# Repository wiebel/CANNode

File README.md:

Homegrown CAN/OW based home automation.

https://wiebel.org/CANNode/

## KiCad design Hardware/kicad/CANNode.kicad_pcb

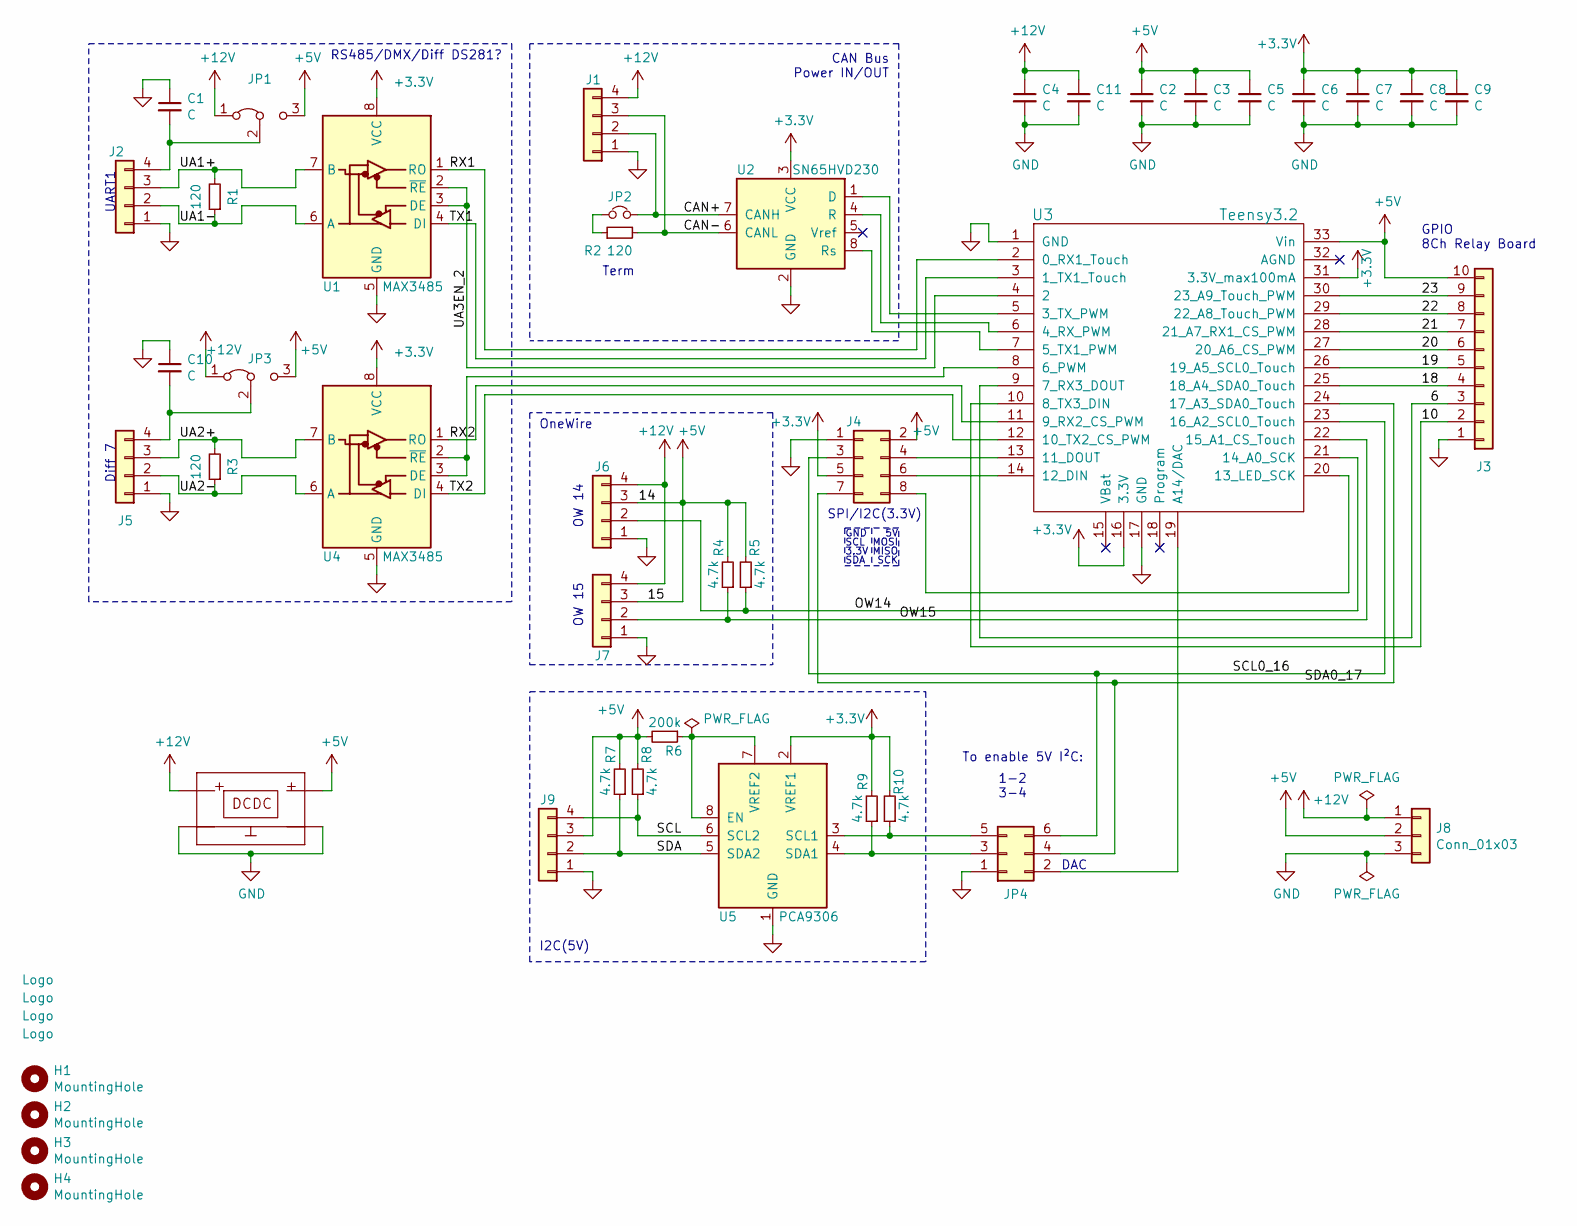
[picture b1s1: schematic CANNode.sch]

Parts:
C1, C2, C3, C4, C5, C6, C7, C8, C9, C10, C11: C; C_0805_2012Metric_Pad1.15x1.40mm_HandSolder
H1, H2, H3, H4: MountingHole; MountingHole_2.7mm
J1, J6: Conn_01x04; WAGO_243_4-Pole
J2, J5: Conn_01x04; OWN_KF141V-P4_simple
J3: Conn_01x10; PinHeader_1x10_P2.54mm_Vertical
J4: Conn_02x04_Odd_Even; PinHeader_2x04_P2.54mm_Vertical
J7, J9: Conn_01x04; PinHeader_1x04_P2.54mm_Vertical
J8: Conn_01x03; WAGO_243_3-Pole
JP1, JP3: Jumper_3_Bridged12; SolderJumper-3_P1.3mm_Bridged2Bar12_RoundedPad1.0x1.5mm_Num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
JP2: Jumper_NC_Small; PinHeader_1x02_P2.54mm_Vertical
JP4: Conn_02x03_Odd_Even; PinHeader_2x03_P2.54mm_Vertical
Log1, Log3: Logo; LOGO_MID
Log2, Log4: Logo; OSHW-Logo_5.7x6mm_Copper
MOD1: DSN-MINI-360; OWN_DC-DC
R1, R2, R3: 120; R_0805_2012Metric_Pad1.15x1.40mm_HandSolder
R4, R5, R7, R8, R9, R10: 4.7k; R_0805_2012Metric_Pad1.15x1.40mm_HandSolder
R6: 200k; R_0805_2012Metric_Pad1.15x1.40mm_HandSolder
U1, U4: MAX3485; SOIC-8_3.9x4.9mm_P1.27mm
U2: SN65HVD230; SOIC-8_3.9x4.9mm_P1.27mm
U3: Teensy3.2; Teensy3_min
U5: PCA9306; SOIC-8_3.9x4.9mm_P1.27mm

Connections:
+3V3: C6.1, C7.1, C8.1, C9.1, J4.5, R9.2, R10.2, U1.8 (VCC), U2.3 (VCC), U3.16 (3.3V), U3.31 (3.3V_max100mA), U4.8 (VCC), U5.2 (VREF1)
+5V: C2.1, C3.1, C5.1, J3.10, J4.2, J6.3, J7.3, J8.2, J9.3, JP1.3 (B), JP3.3 (B), MOD1.OUT+, R4.2, R5.2, R6.2, R7.2, R8.2, U3.33 (Vin)
+12V: C4.1, C11.1, J1.4, J6.4, J7.4, J8.1, JP1.1 (A), JP3.1 (A), MOD1.IN+
/6: J3.3, U3.9 (7_RX3_DOUT)
/10: J3.2, U3.10 (8_TX3_DIN)
/18: J3.4, U3.25 (18_A4_SDA0_Touch)
/19: J3.5, U3.26 (19_A5_SCL0_Touch)
/20: J3.6, U3.27 (20_A6_CS_PWM)
/21: J3.7, U3.28 (21_A7_RX1_CS_PWM)
/22: J3.8, U3.29 (22_A8_Touch_PWM)
/23: J3.9, U3.30 (23_A9_Touch_PWM)
/CAN+: J1.2, JP2.2, U2.7 (CANH)
/CAN-: J1.3, R2.2, U2.6 (CANL)
/OW14: J6.2, R5.1, U3.21 (14_A0_SCK)
/OW15: J7.2, R4.1, U3.22 (15_A1_CS_Touch)
/RX1: U1.1 (RO), U3.2 (0_RX1_Touch)
/RX2: U3.11 (9_RX2_CS_PWM), U4.1 (RO)
/SCL: J9.4, R8.1, U5.6 (SCL2)
/SCL0_16: J4.3, JP4.6, U3.23 (16_A2_SCL0_Touch)
/SDA: J9.2, R7.1, U5.5 (SDA2)
/SDA0_17: J4.7, JP4.4, U3.24 (17_A3_SDA0_Touch)
/TX1: U1.4 (DI), U3.3 (1_TX1_Touch)
/TX2: U3.12 (10_TX2_CS_PWM), U4.4 (DI)
/UA1+: J2.3, R1.2, U1.7 (B)
/UA1-: J2.2, R1.1, U1.6 (A)
/UA2+: J5.3, R3.2, U4.7 (B)
/UA2-: J5.2, R3.1, U4.6 (A)
/UA3EN_2: U1.2 (~RE), U1.3 (DE), U3.4 (2)
GND: C1.1, C2.2, C3.2, C4.2, C5.2, C6.2, C7.2, C8.2, C9.2, C10.1, C11.2, J1.1, J2.1, J3.1, J4.1, J5.1, J6.1, J7.1, J8.3, J9.1, JP4.1, MOD1.IN-, MOD1.OUT-, U1.5 (GND), U2.2 (GND), U3.1 (GND), U3.17 (GND), U4.5 (GND), U5.1 (GND)
unnamed: C1.2, J2.4, JP1.2 (C)
unnamed: C10.2, J5.4, JP3.2 (C)
unnamed: J4.4, U3.13 (11_DOUT)
unnamed: J4.6, U3.14 (12_DIN)
unnamed: J4.8, U3.20 (13_LED_SCK)
unnamed: JP2.1, R2.1
unnamed: JP4.2, U3.19 (A14/DAC)
unnamed: JP4.3, R9.1, U5.4 (SDA1)
unnamed: JP4.5, R10.1, U5.3 (SCL1)
unnamed: R6.1, U5.7 (VREF2), U5.8 (EN)
unnamed: U2.1 (D), U3.5 (3_TX_PWM)
unnamed: U2.4 (R), U3.6 (4_RX_PWM)
unnamed: U2.8 (Rs), U3.7 (5_TX1_PWM)
unnamed: U3.8 (6_PWM), U4.2 (~RE), U4.3 (DE)

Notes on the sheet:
CAN Bus Power IN/OUT
Term
RS485/DMX/Diff DS281?
OneWire
SPI/I2C(3.3V)
GPIO 8Ch Relay Board
DAC
I2C(5V)
Diff 7
UART1
OW 14
OW 15
GND
3.3V
SCL
SDA
MOSI
MISO
SCK
To enable 5V I²C:
1-2 3-4

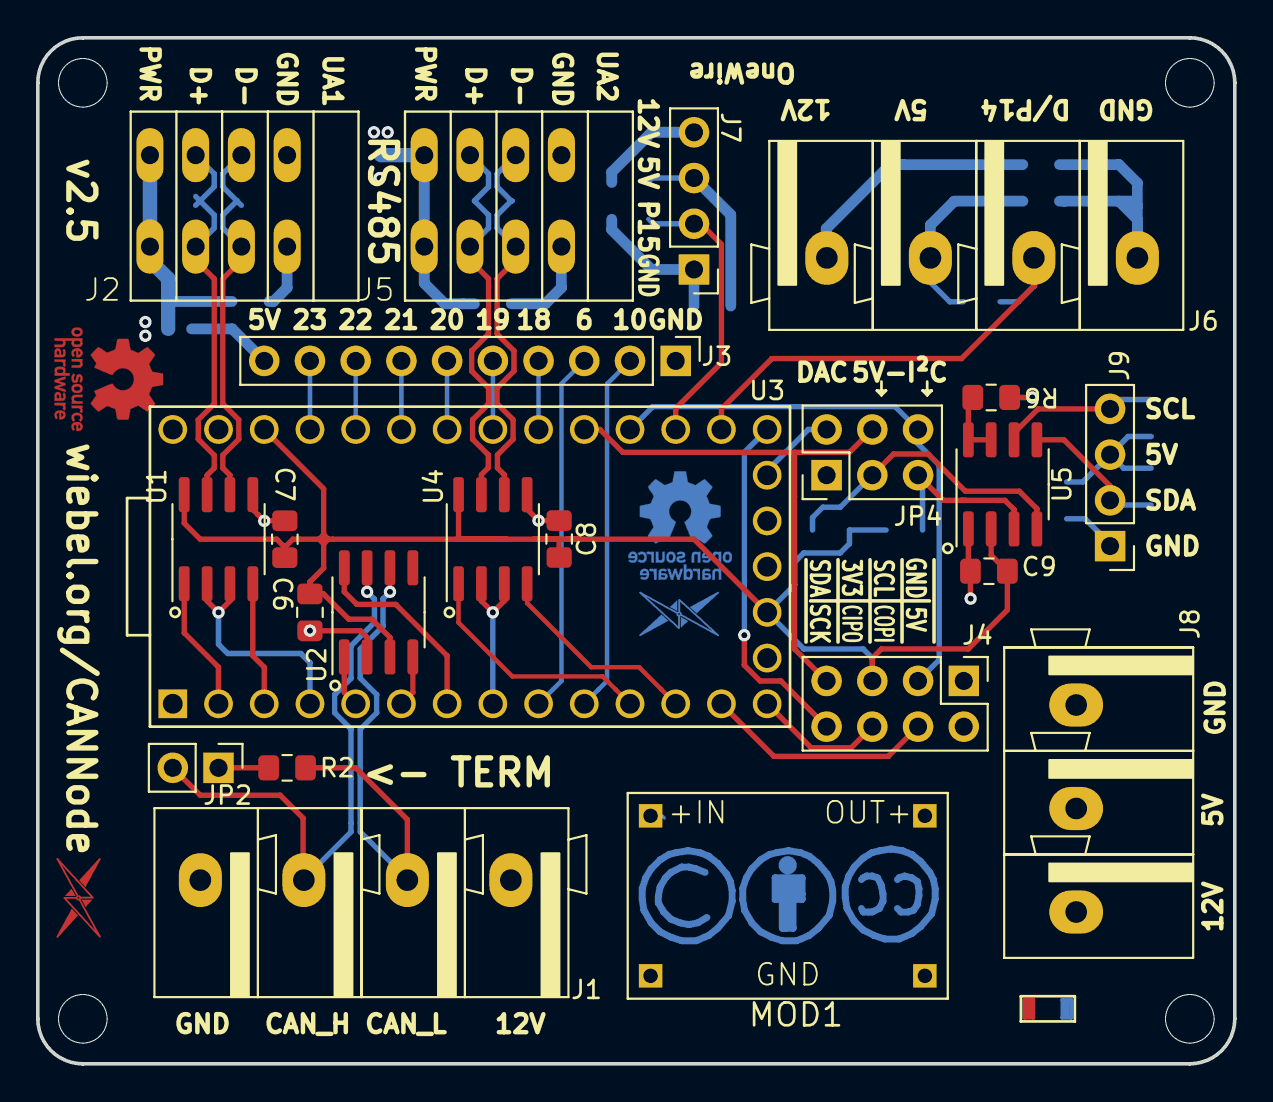
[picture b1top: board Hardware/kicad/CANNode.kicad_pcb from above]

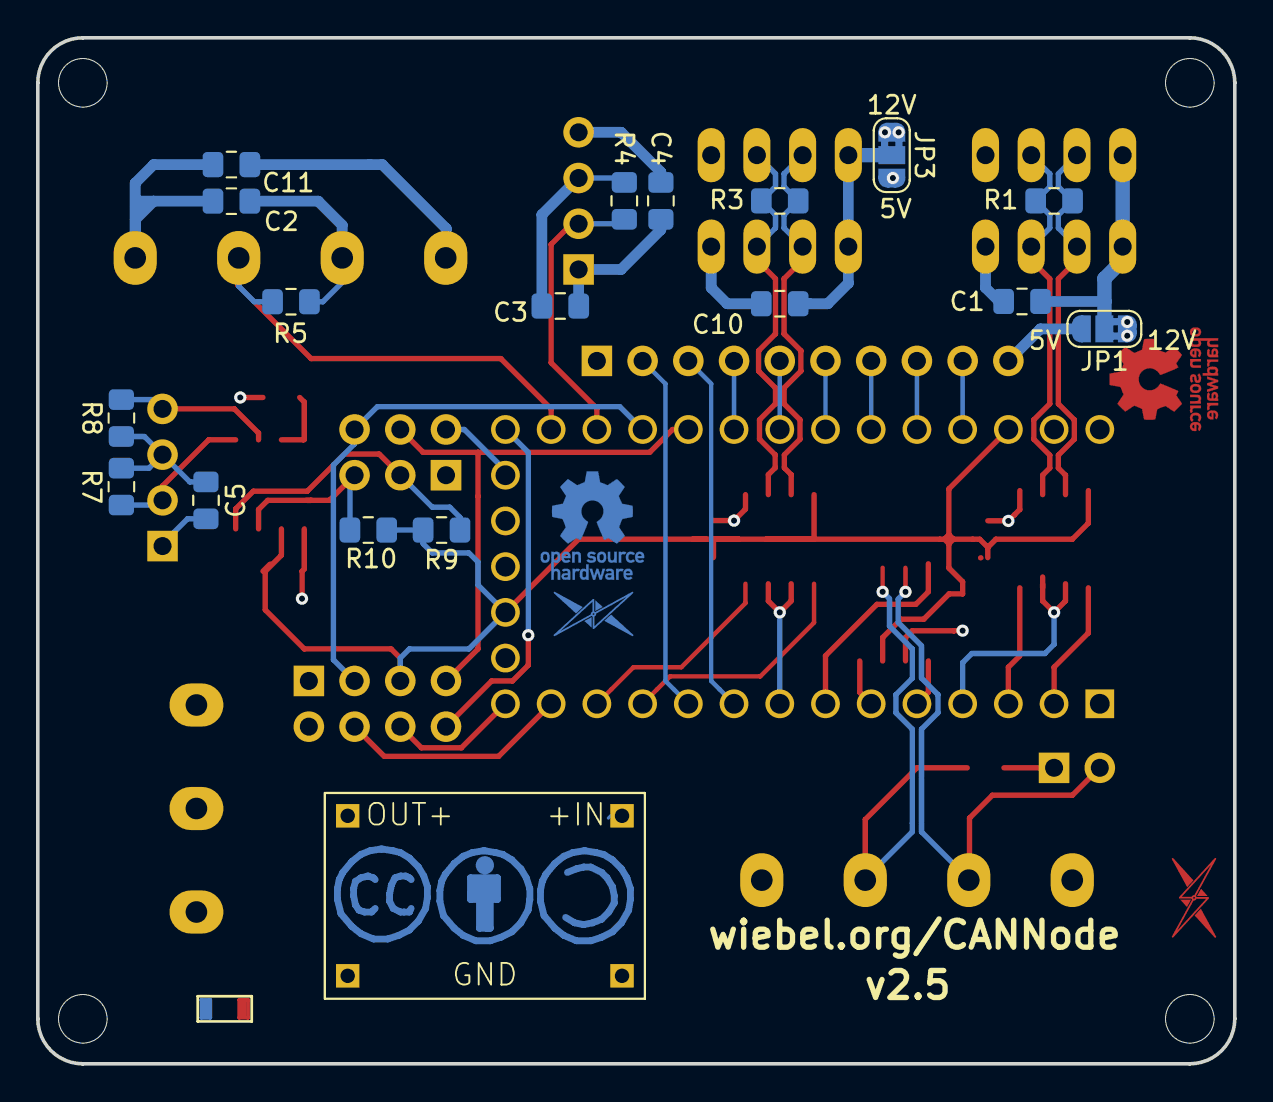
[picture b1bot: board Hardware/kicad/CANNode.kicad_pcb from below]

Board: 4 copper layers, 66.5 x 57.0 mm, 48 parts (19 on the bottom side), 43 nets.

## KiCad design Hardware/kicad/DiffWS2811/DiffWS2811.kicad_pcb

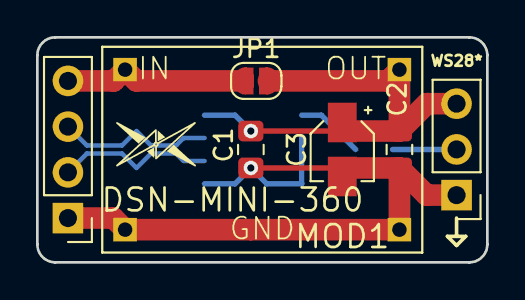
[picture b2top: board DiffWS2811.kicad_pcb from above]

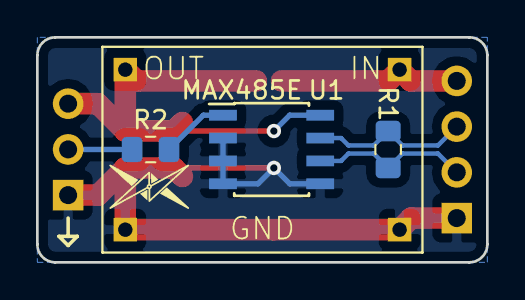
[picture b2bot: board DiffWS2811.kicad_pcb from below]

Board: 2 copper layers, 25.0 x 12.5 mm, 10 parts (3 on the bottom side), 7 nets.

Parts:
C1, C2: C_Small; C_0805_2012Metric_Pad1.15x1.40mm_HandSolder
C3: CP_Small; CP_Elec_3x5.4
J1: Conn_01x04; PinHeader_1x04_P2.54mm_Vertical
J2: Conn_01x03; PinHeader_1x03_P2.54mm_Vertical
JP1: Jumper; SolderJumper-2_P1.3mm_Open_RoundedPad1.0x1.5mm
MOD1: DSN-MINI-360; DC-DC
R1, R2: R_Small; R_0805_2012Metric_Pad1.15x1.40mm_HandSolder
U1: MAX485E; SOIC-8_3.9x4.9mm_P1.27mm

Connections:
-VSW: J1.4, JP1.1, MOD1.IN
/D+: J1.3, R1.1, U1.7
/D-: J1.2, R1.2, U1.6
GND: C1.2, C2.2, C3.2, J1.1, J2.1, MOD1.GND, U1.2, U1.3, U1.4, U1.5
unnamed: J2.2, R2.1
unnamed: R2.2, U1.1
VCC: C1.1, C2.1, C3.1, J2.3, JP1.2, MOD1.OUT, U1.8

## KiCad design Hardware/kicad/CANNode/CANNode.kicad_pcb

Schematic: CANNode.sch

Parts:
C1, C2: CP; CP_Elec_3x5.4
C3, C4, C5, C6, C7, C8, C9, C10: C; C_0805_2012Metric_Pad1.15x1.40mm_HandSolder
J1, J2, J11, J31, J41, J91: Conn_01x04; OWN_KF141V-P4_simple
J12, J21, J42, J43, J44: Conn_01x04; PinHeader_1x04_P2.54mm_Vertical
J51: Conn_01x02; PinHeader_1x02_P2.54mm_Vertical
J61: Conn_02x04_Odd_Even; PinHeader_2x04_P2.54mm_Vertical
J81: Conn_01x10; PinHeader_1x10_P2.54mm_Vertical
JP1, JP21, JP22: Jumper_NC_Small; PinHeader_1x02_P2.54mm_Vertical
JP31, JP41: Jumper_3_Bridged12; SolderJumper-3_P1.3mm_Bridged2Bar12_RoundedPad1.0x1.5mm_Num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
MOD1: OWN_DCDC; OWN_DC-DC
R1, R2, R3, R4, R5, R6: 120; R_0805_2012Metric_Pad1.15x1.40mm_HandSolder
R11, R12, R21, R22, R24, R25: 4.7k; R_0805_2012Metric_Pad1.15x1.40mm_HandSolder
R23: 200k; R_0805_2012Metric_Pad1.15x1.40mm_HandSolder
U1: Teensy3.2; Teensy3_min
U2: SN65HVD230; SOIC-8_3.9x4.9mm_P1.27mm
U21: PCA9306; SOIC-8_3.9x4.9mm_P1.27mm
U31: MAX3485; SOIC-8_3.9x4.9mm_P1.27mm
U41: MAX3485; SOIC-16_3.9x9.9mm_P1.27mm
U91: LM1117-5.0; SOT-223-3_TabPin2

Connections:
+3V3: C7.1, C8.1, C9.1, C10.1, J61.5, J91.2, R21.2, R22.2, U1.16, U1.31, U2.3 (VCC), U21.2 (VREF1), U31.8 (VCC), U41.4, U41.16
+5V: C2.1, C3.1, C4.1, C5.1, C6.1, J11.3, J12.3, J21.3, J42.4, J43.4, J44.4, J61.2, J81.10, J91.3, JP31.3 (B), JP41.3 (B), MOD1.OUT+, R11.2, R12.2, R23.2, R24.2, R25.2, U1.33, U91.2
+12V: C1.1, J1.4, J2.4, J11.4, J12.4, J91.4, JP31.1 (A), JP41.1 (A), MOD1.IN+, U91.3
/6: J81.3, U1.8
/10: J81.2, U1.12
/16: J81.4, U1.25
/17: J81.5, U1.26
/20: J81.6, U1.27
/21: J81.7, U1.28
/22: J81.8, U1.29
/23: J81.9, U1.30
/CAN+: J1.2, J2.2, JP1.2, U2.7 (CANH)
/CAN-: J1.3, J2.3, R1.2, U2.6 (CANL)
/D1+: J41.3, R2.2, U41.2
/D1-: J41.2, R2.1, U41.3
/D2+: J42.3, R4.2, U41.6
/D2-: J42.2, R4.1, U41.5
/D3+: J43.3, R3.2, U41.10
/D3-: J43.2, R3.1, U41.11
/D4+: J44.3, R5.2, U41.14
/D4-: J44.2, R5.1, U41.13
/DI1_7: U1.9, U41.1
/DI2_8: U1.10, U41.7
/EN34_9: U1.11, U41.12
/OW14: J11.2, R12.1, U1.21
/RX1: U1.2, U31.1 (RO)
/SCL: J21.4, R25.1, U21.6 (SCL2)
/SCL0_16: J61.3, JP21.2, U1.23, U41.9
/SDA: J21.2, R24.1, U21.5 (SDA2)
/TX2: U1.3, U31.4 (DI)
/UA1+: J31.2, R6.1, U31.6 (A)
/UA1-: J31.3, R6.2, U31.7 (B)
/UA3EN_2: U1.4, U31.2 (~RE), U31.3 (DE)
GND: C1.2, C2.2, C3.2, C4.2, C5.2, C6.2, C7.2, C8.2, C9.2, C10.2, J1.1, J2.1, J11.1, J12.1, J21.1, J31.1, J41.1, J42.1, J43.1, J44.1, J51.1, J61.1, J81.1, J91.1, MOD1.IN-, MOD1.OUT-, U1.1, U1.17, U2.2 (GND), U21.1 (GND), U31.5 (GND), U41.8, U91.1
unnamed: J12.2, R11.1, U1.22
unnamed: J31.4, JP31.2 (C)
unnamed: J41.4, JP41.2 (C)
unnamed: J51.2, U1.19
unnamed: J61.4, U1.13
unnamed: J61.6, U1.14
unnamed: J61.7, JP22.2, U1.24, U41.15
unnamed: J61.8, U1.20
unnamed: JP1.1, R1.1
unnamed: JP21.1, R21.1, U21.3 (SCL1)
unnamed: JP22.1, R22.1, U21.4 (SDA1)
unnamed: R23.1, U21.7 (VREF2), U21.8 (EN)
unnamed: U1.5, U2.1 (D)
unnamed: U1.6, U2.4 (R)
unnamed: U1.7, U2.8 (Rs)

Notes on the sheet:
CAN Bus Power IN/OUT
Term
RS485/DMX/Diff DS281?
OneWire
SPI/I2C(3.3V)
GPIO 8Ch Relay Board
DAC
I2C(5V)
Diff 7
Diff8
Diff 16
Diff 17
UART1
OW 14
OW 15
GND
3.3V
SCL
SDA
MOSI
MISO
SCK

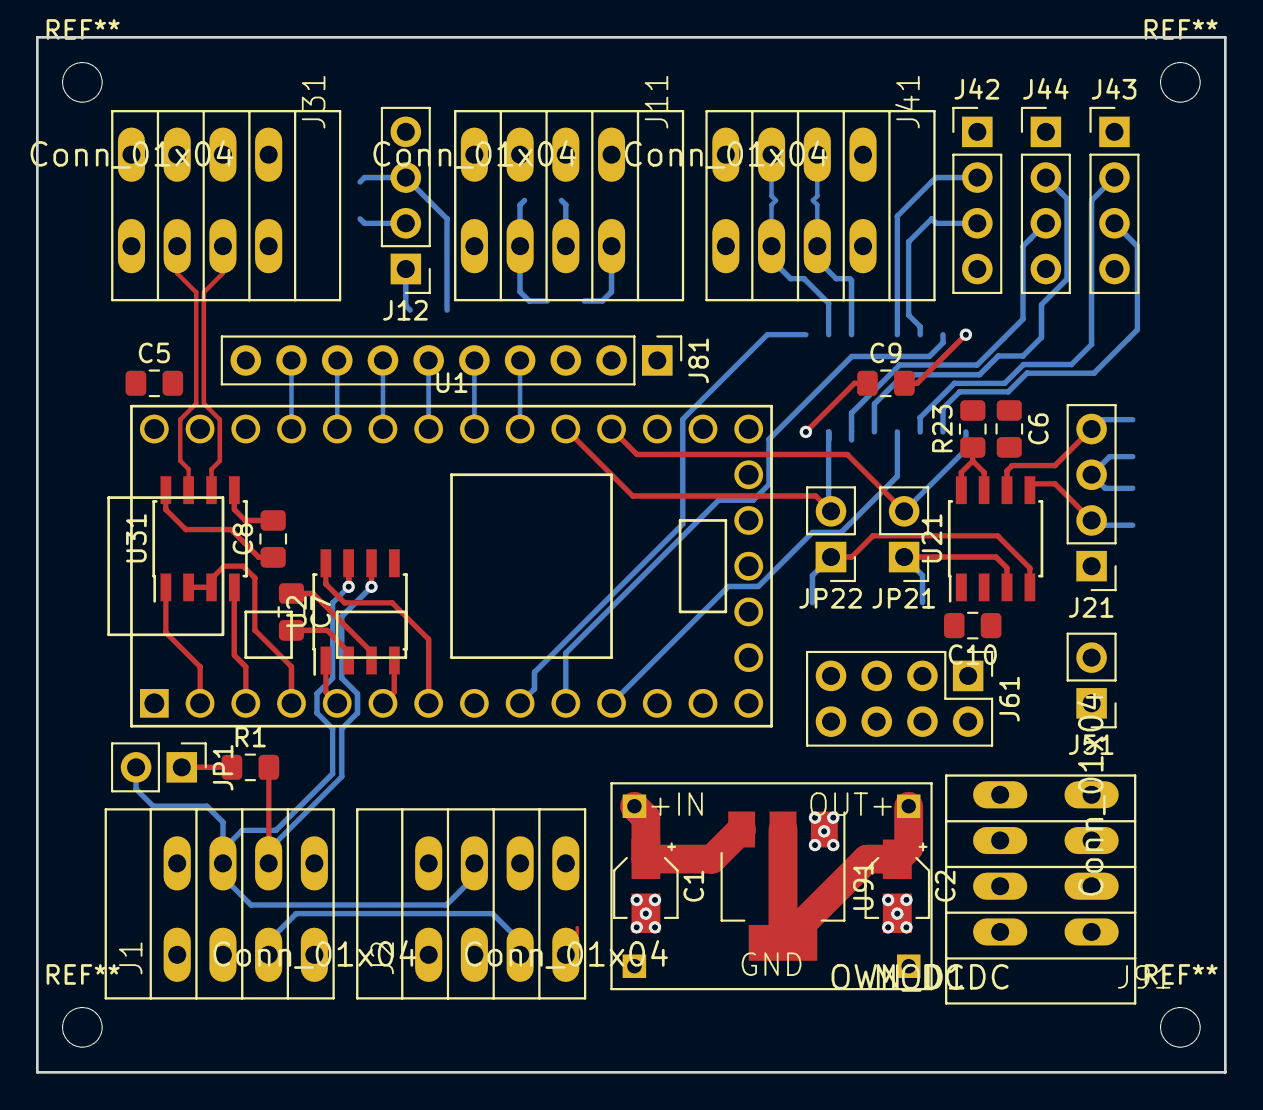
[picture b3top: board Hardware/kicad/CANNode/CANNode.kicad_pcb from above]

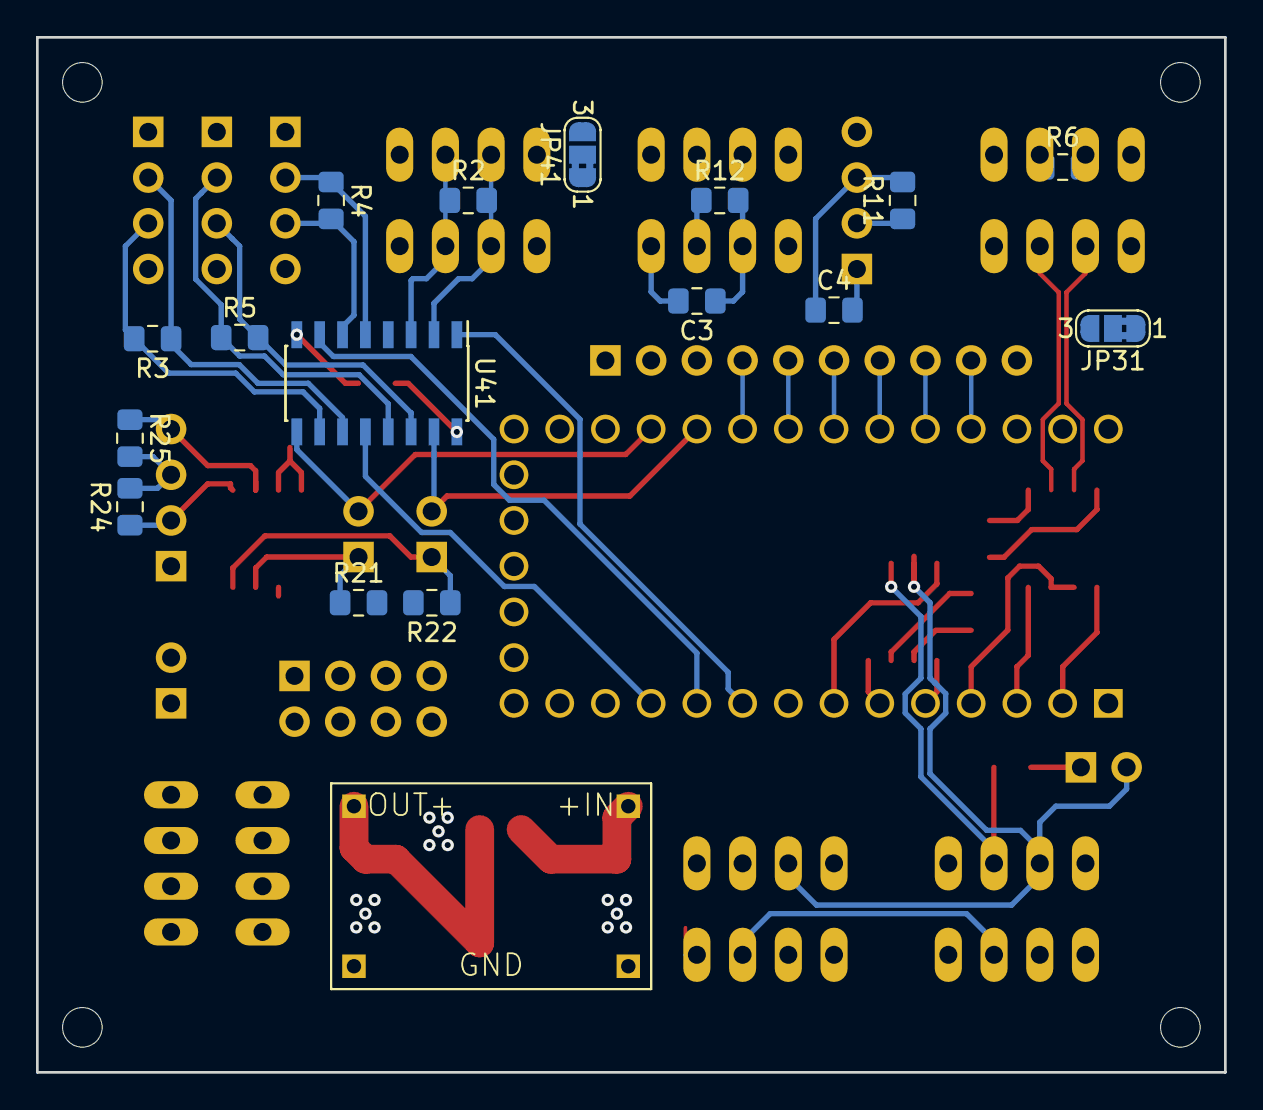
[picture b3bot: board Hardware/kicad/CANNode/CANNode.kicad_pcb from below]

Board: 4 copper layers, 66.0 x 57.5 mm, 49 parts (16 on the bottom side), 49 nets.

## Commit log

2016-05-30 initial
2016-05-30 Latest
2016-06-01 getting structurerered
2016-06-01 state change implemented
2016-06-02 first CAN light ;)
2016-06-03 renamed (see PCB)
2016-06-03 cleanup
2016-06-03 added Hardware sources
2016-06-03 Added Schematic as png
2016-06-11 now with response and remote switching
2016-07-24 starting with output
2016-09-09 in progress
2016-09-09 Compiling again
2016-09-14 It Works !!
2016-09-18 Before can send rewrite
2016-09-18 kinda working, still queing problems
2016-09-18 Great success, read and write buffering CAN wise
2016-09-18 first Switches
2016-09-19 tuning starts
2016-09-24 Productive
2016-09-25 iworking 2
2016-09-27 better initialization, consistant switches
2017-01-15 Before ModularizatioBefore Modularizationn
2017-01-15 new external node definition
2017-02-15 node 3 went life
2017-02-15 improved error handling of OW devices
2017-03-22 Configurrations
2017-03-22 mirror test
2017-03-22 mirror test 02
2017-03-22 Revert "mirror test"
    This reverts commit f052826ef3645006a35cdb1b423a686126aebfa9.
2017-07-25 latest addition (rolladen, Terasse)
2017-09-21 new node and FastLED
2017-10-02 git test
2017-10-02 Revert "new node and FastLED"
    This reverts commit 4730087f9e0407dac3795dfea3b10a3f22bc8b54.
2017-10-05 Revert "latest addition (rolladen, Terasse)"
    This reverts commit 26ac6558e48cb40bebec67ddc240ef2eee2f421f.
2017-10-05 Revert "git test"
    This reverts commit f4ac188a96c213f6665db2e03689f4f45f09be38.
2018-01-19 Latest addition WZ switch
2018-03-01 Refinements
2018-03-01 push test
2018-03-07 Add 'README.md'
    Started a README
2018-03-07 More to READ
2018-08-20 new images
2018-09-14 Create LICENSE
2018-10-30 More talking to CAN (state change, new TWids)
2018-11-12 rev2 started on kicad
2018-11-13 kicad 101
2018-11-15 Rearranging
2018-11-16 almost routed
2018-11-17 looks good
2018-11-17 images
2018-11-17 late changes
2018-11-17 images from oshpark
2018-11-22 Licenced by CC
2018-11-22 more clearance in Layer 2
2018-11-22 cleanup after order
2018-11-22 images moved to webroot
2018-11-22 corrected output port labels
2018-12-03 ena I²C text
2019-03-17 new switch in WZ
2019-03-20 more feedback in and out
2019-03-24 added some tools
2019-03-28 more tools
2019-04-01 added affinity groups
2019-04-02 much better can bus writing
2019-09-02 last before adding current sensors
2019-10-22 First current messurement attempts
2019-10-22 new images (pdf)
2019-11-16 double RS485
2019-11-16 second RS485 swapped with OW
2019-12-15 latest changes in tools
2019-12-16 fixed loop for shutter2can
2019-12-16 updated coilmap
2019-12-29 some toole refinery
2019-12-29 new alli in one, 001
2020-01-15 try for command to fix failure in unknowtry for command to fix failure in unknownn
2020-02-25 latest additions
2020-07-01 pproaching v2.5
2021-02-18 PCB fixed silkscreen
